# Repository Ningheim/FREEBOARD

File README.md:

# FREEBOARD
A 60% RGB Backlit Keyboard with a OLED display, rotary encoder, and adjustable inclination stands.

This keyboard is powered by an Orpheus/Raspberry Pi Pico and an additional MCP23017 for extra GPIO pins. The firmware is entirely coded in [QMK](https://qmk.fm/) and the case is a little wider than a Framework 13 for reference, at about 320x165mm it's made to be compact and accessible to be used alongside a laptop. I made this because I wanted to fix a lot of things with the layout of other wormier and logitech keyboards where the keys weren't as inline as I'd hoped whilst still including function keys and appealing RGB factors.

## Here are the pictures to the project
### Intended Layout ([Plate Generator](https://kbplate.ai03.com/)):

### Schematic (KiCAD):

### PCB (KiCAD):

### CASE (Onshape [[Document Link]](https://cad.onshape.com/documents/8cd69c605bee1d154198ffc3/w/f18789aa034f433dfb01300c/e/379cd418fcd399b0823d03fd?renderMode=0&uiState=6a71e7e218279ebdb2fef9ea))

## Case Assembly
You can use adhesive for some of the parts but it isn't required as they should sit flush without any glue, you can also sand things down to fit flush if your 3d printed had a printing issue. All of the parts I'm naming in this section have corresponding names in the onshape document.

1. Put the `Plastic Spacer` in first, then the `Plastic Window` into the slot on the inside of the `Base Case`, The window is meant to be made out of clear material like transparent plastic or something so you can see the Silkscreen design on the bottom side of the board.
2. Cut a two 1mm diameter rods to 64mm and Thread each one through the holes of each set of tilt stands you as shown in the assembly tab on the onshape document. The stands should be able to turn/revolve around the axis of the rods, and you can make the rods of any material it just has to be firm. To lock the rods in, melt plastic or insert rubber friction pads into each of the 6 empty rectangular indents on the back of the `Base Case`
3. Then you can put in the PCB with the `Plate` ontop of it. Now we have the `Top Cover` and `Translucent Emblem` left, so put the `Translucent Emblem` into the matching cutout on the `Top Cover`, and insert those joined pieces into the top of the case, to keep everything pressed down. Lastly, add the encoder knob and you're done!

## How To Flash
Freeboard uses QMK Firmware running on a Raspberry Pi Pico. The firmware source is available in firmware/freeboard.

The firmware supports:
An 81-key matrix
91 SK6812MINI-E RGB LEDs
An I2C OLED display
A rotary encoder connected through an MCP23017 GPIO expander
Media and RGB controls through a function layer

To start building the firmware, install and configure the QMK development environment, then copy the Freeboard firmware into your QMK installation:

cp -a firmware/freeboard ~/qmk_firmware/keyboards/
cd ~/qmk_firmware
qmk clean
qmk compile -kb freeboard -km default

After a successful build, the flashable firmware will be located at:

~/qmk_firmware/freeboard_default.uf2

#### Flashing Sequence
Unplug Freeboard from the computer.
Hold the BOOTSEL button on the Raspberry Pi Pico.
While continuing to hold BOOTSEL, connect the keyboard to the computer using USB.
Release BOOTSEL when a removable drive named RPI-RP2 appears.
Copy freeboard_default.uf2 onto the RPI-RP2 drive.
The drive will disconnect automatically and the keyboard will restart with the new firmware.
Flashing future updates

Hold Fn and press Esc to enter the RP2040 bootloader. When the RPI-RP2 drive appears, copy the newly compiled freeboard_default.uf2 onto it.

## CONTROLS
The Fn key is located between Right Alt and Left Arrow.

Input	Action
Rotate encoder	Adjust volume
Press encoder	Mute or unmute
Fn + Esc	Enter the bootloader
Fn + Home	Toggle RGB lighting
Fn + Page Up	Select the next RGB effect
Fn + Page Down	Select the previous RGB effect
Fn + Up	Increase RGB brightness
Fn + Down	Decrease RGB brightness
Fn + Left	Decrease RGB hue
Fn + Right	Increase RGB hue
Fn + End	Increase RGB animation speed
RGB brightness is limited in firmware because all 91 LEDs are powered from USB VBUS. Increasing the limit could exceed the available USB current.

## BOM
| Item | Cost |
|------|------|
| PCB | $37.84 |
| Switches, Keycaps, Encoder, Display | $15.00 |
| Plastic Case | Free (Printing Legion) |
| Electronic Components | $22.18 |
| Display Connector | $7.00 |
| Buffer for shipping and fees | $5.00 |
| **Total** | **~$88.02** |

Note: The BOM file itself is in ~\FREEPCB\PRODUCTION, and the keycaps, switches, stabilizers, and encoder all probably have to be bought from an external retailer. So prices may vary.

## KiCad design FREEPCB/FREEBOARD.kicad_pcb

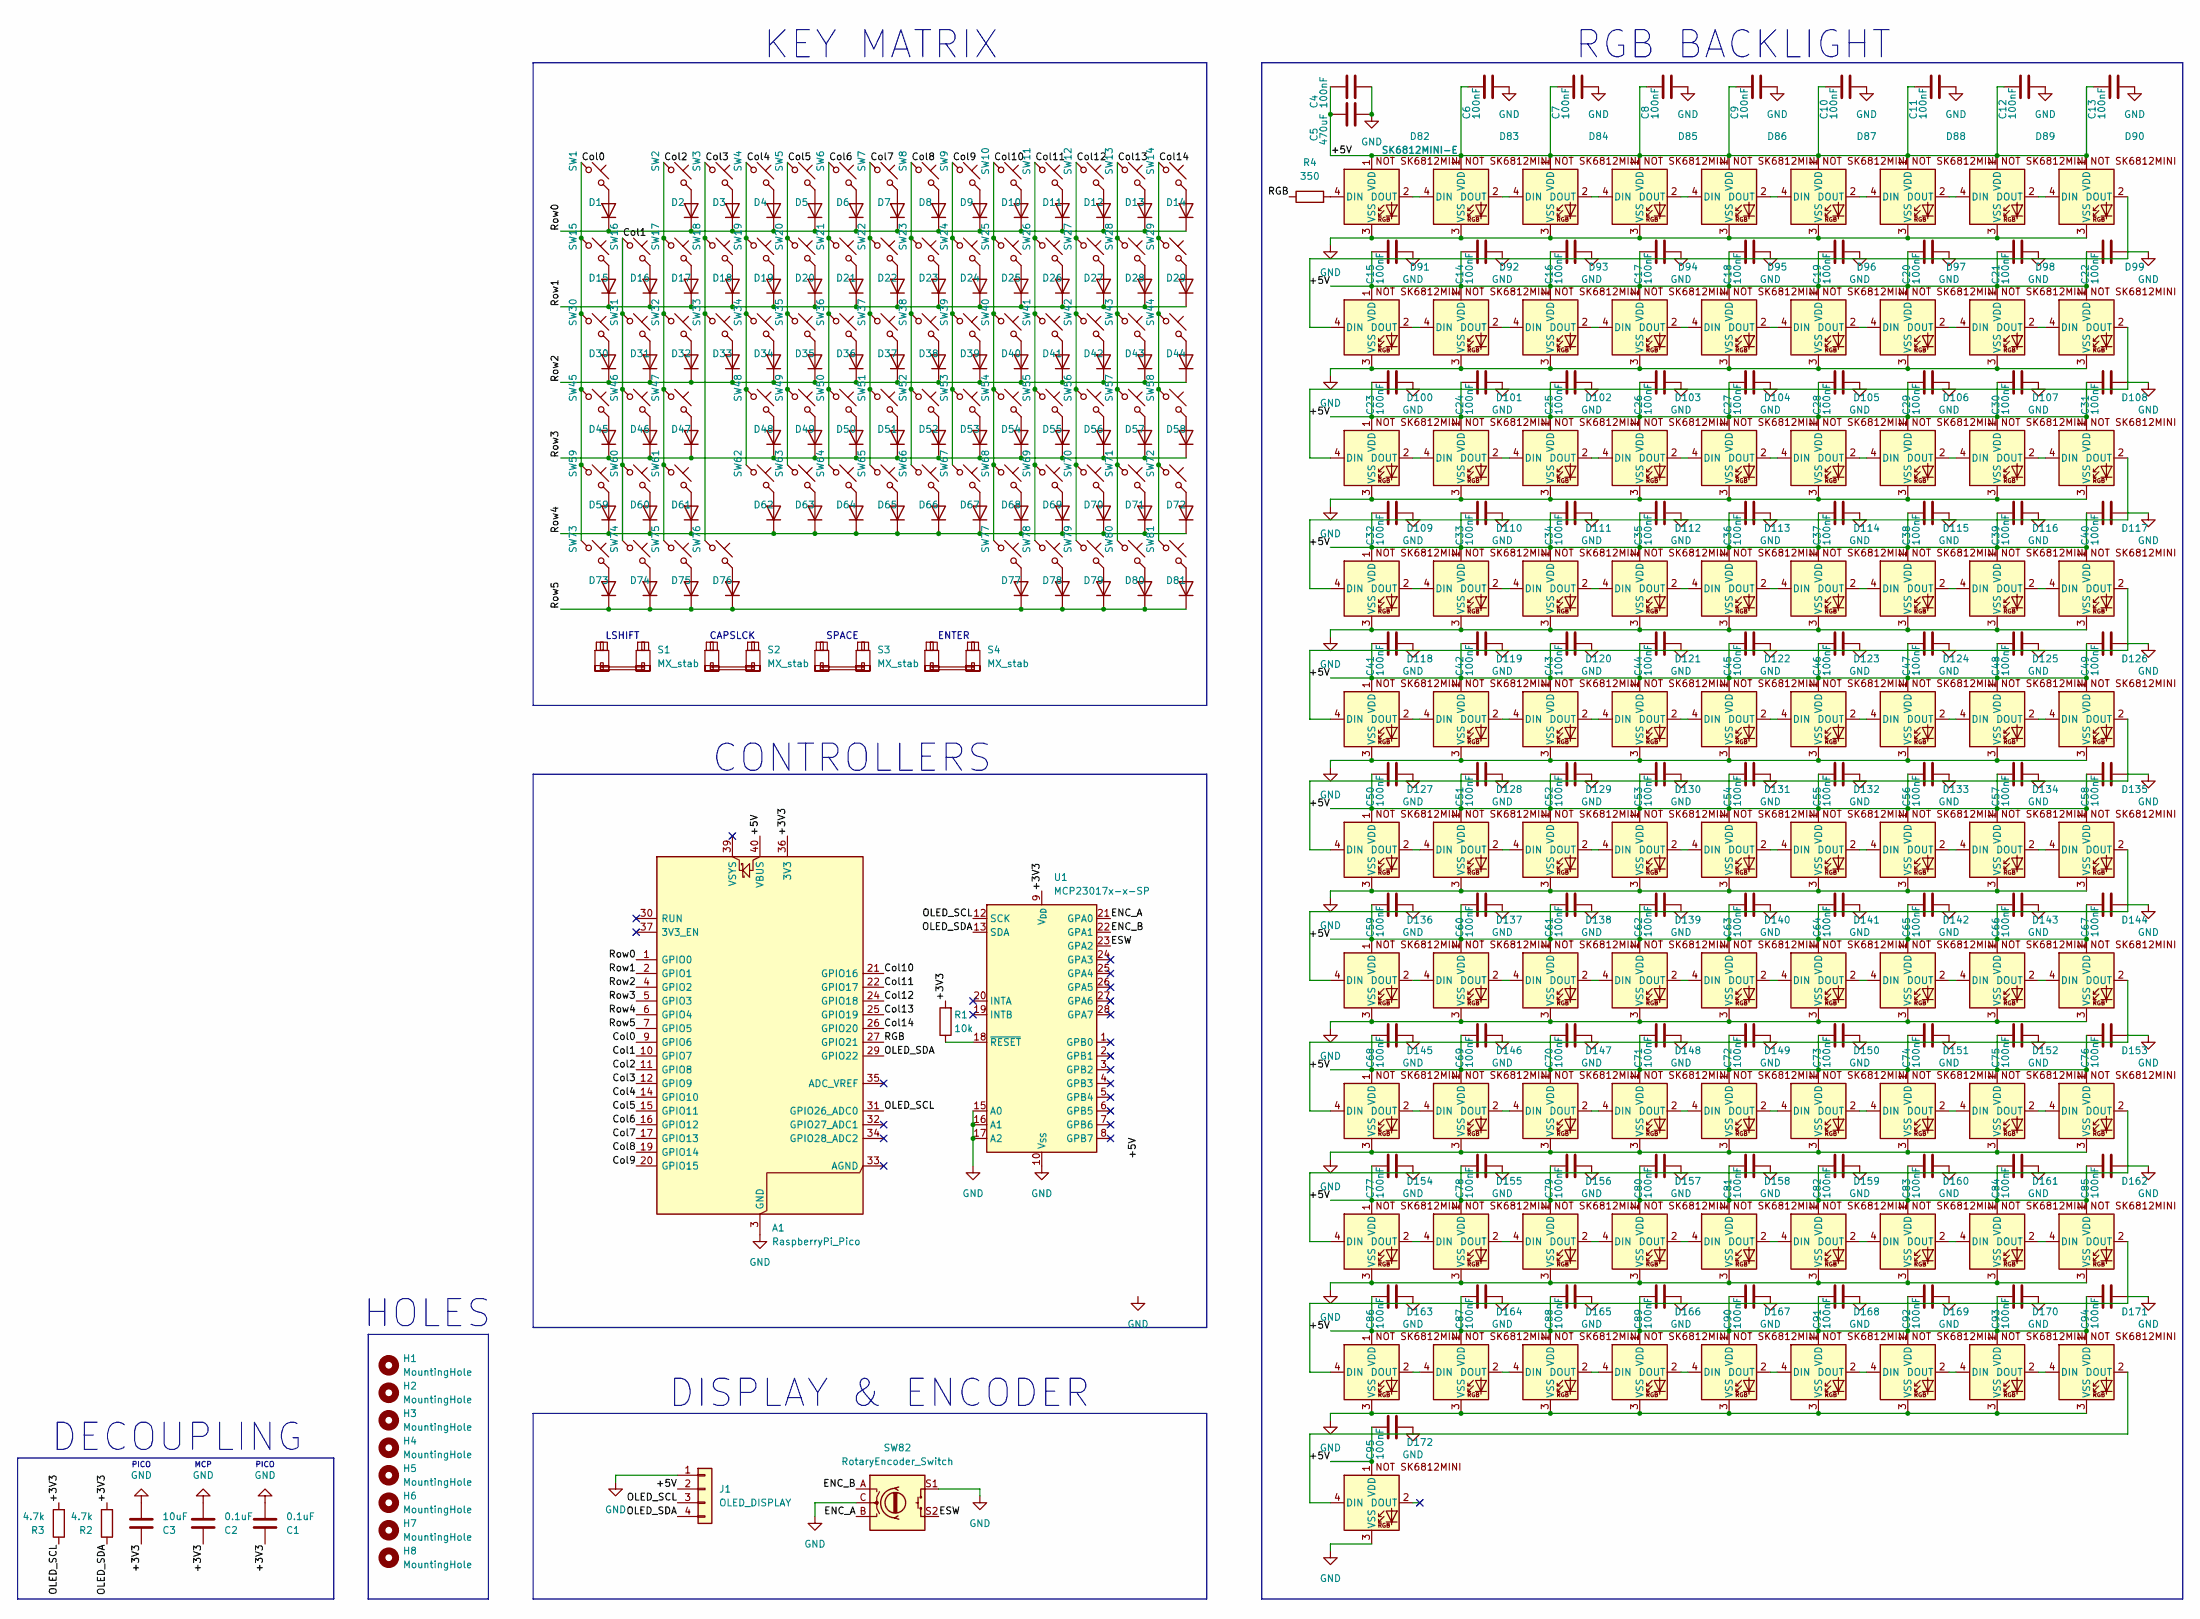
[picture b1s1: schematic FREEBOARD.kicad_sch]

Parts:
A1: RaspberryPi_Pico; RaspberryPi_Pico_Common_THT
C1, C2: 0.1uF; C_0603_1608Metric_Pad1.08x0.95mm_HandSolder
C3: 10uF; C_0805_2012Metric_Pad1.18x1.45mm_HandSolder
C4, C6, C7, C8, C9, C10, C11, C12, C13, C14, C15, C16, C17, C18, C19, C20, C21, C22, C23, C24, C25, C26, C27, C28, C29, C30, C31, C32, C33, C34, C35, C36, C37, C38, C39, C40, C41, C42, C43, C44, C45, C46, C47, C48, C49, C50, C51, C52, C53, C54, C55, C56, C57, C58, C59, C60, C61, C62, C63, C64, C65, C66, C67, C68, C69, C70, C71, C72, C73, C74, C75, C76, C77, C78, C79, C80, C81, C82, C83, C84, C85, C86, C87, C88, C89, C90, C91, C92, C93, C94, C95: 100nF; C_0603_1608Metric_Pad1.08x0.95mm_HandSolder
C5: 470uF; CP_EIA-7343-31_Kemet-D_HandSolder
D1, D2, D3, D4, D5, D6, D7, D8, D9, D10, D11, D12, D13, D14, D15, D16, D17, D18, D19, D20, D21, D22, D23, D24, D25, D26, D27, D28, D29, D30, D31, D32, D33, D34, D35, D36, D37, D38, D39, D40, D41, D42, D43, D44, D45, D46, D47, D48, D49, D50, D51, D52, D53, D54, D55, D56, D57, D58, D59, D60, D61, D62, D63, D64, D65, D66, D67, D68, D69, D70, D71, D72, D73, D74, D75, D76, D77, D78, D79, D80, D81: 1N4148; D_DO-35_SOD27_P7.62mm_Horizontal
D82, D83, D84, D85, D86, D87, D88, D89, D90, D91, D92, D93, D94, D95, D96, D97, D98, D99, D100, D101, D102, D103, D104, D105, D106, D107, D108, D109, D110, D111, D112, D113, D114, D115, D116, D117, D118, D119, D120, D121, D122, D123, D124, D125, D126, D127, D128, D129, D130, D131, D132, D133, D134, D135, D136, D137, D138, D139, D140, D141, D142, D143, D144, D145, D146, D147, D148, D149, D150, D151, D152, D153, D154, D155, D156, D157, D158, D159, D160, D161, D162, D163, D164, D165, D166, D167, D168, D169, D170, D171, D172: SK6812MINI-E; SK6812MINI-E_fixed
H1, H2, H3, H4, H5, H6, H7, H8: MountingHole; MountingHole_3.2mm_M3
J1: OLED_DISPLAY; JST_SH_BM04B-SRSS-TB_1x04-1MP_P1.00mm_Vertical
R1: 10k; R_0603_1608Metric_Pad0.98x0.95mm_HandSolder
R2, R3: 4.7k; R_0603_1608Metric_Pad0.98x0.95mm_HandSolder
R4: 350; R_0603_1608Metric_Pad0.98x0.95mm_HandSolder
S1: MX_stab; STAB_MX_2u
S2, S3: MX_stab; STAB_MX_2.25u
S4: MX_stab; STAB_MX_6.25u
SW1, SW2, SW3, SW4, SW5, SW6, SW7, SW8, SW9, SW10, SW11, SW12, SW13, SW14, SW15, SW16, SW17, SW18, SW19, SW20, SW21, SW22, SW23, SW24, SW25, SW26, SW27, SW28, SW29, SW30, SW31, SW32, SW33, SW34, SW35, SW36, SW37, SW38, SW39, SW40, SW41, SW42, SW43, SW44, SW45, SW46, SW47, SW48, SW49, SW50, SW51, SW52, SW53, SW54, SW55, SW56, SW57, SW58, SW59, SW60, SW61, SW62, SW63, SW64, SW65, SW66, SW67, SW68, SW69, SW70, SW71, SW72, SW73, SW74, SW75, SW76, SW77, SW78, SW79, SW80, SW81: SW_Push_45deg; SW_MX_1u
SW82: RotaryEncoder_Switch; ROT_Alps_EC11E-Switch
U1: MCP23017x-x-SP; DIP-28_W7.62mm

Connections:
/+3V3: A1.36 (3V3), C1.1, C2.1, C3.1, R1.2, R2.2, R3.2, U1.9 (V_{DD})
/+5V: A1.40 (VBUS), C4.1, C5.1, C6.1, C7.1, C8.1, C9.1, C10.1, C11.1, C12.1, C13.1, C14.1, C15.1, C16.1, C17.1, C18.1, C19.1, C20.1, C21.1, C22.1, C23.1, C24.1, C25.1, C26.1, C27.1, C28.1, C29.1, C30.1, C31.1, C32.1, C33.1, C34.1, C35.1, C36.1, C37.1, C38.1, C39.1, C40.1, C41.1, C42.1, C43.1, C44.1, C45.1, C46.1, C47.1, C48.1, C49.1, C50.1, C51.1, C52.1, C53.1, C54.1, C55.1, C56.1, C57.1, C58.1, C59.1, C60.1, C61.1, C62.1, C63.1, C64.1, C65.1, C66.1, C67.1, C68.1, C69.1, C70.1, C71.1, C72.1, C73.1, C74.1, C75.1, C76.1, C77.1, C78.1, C79.1, C80.1, C81.1, C82.1, C83.1, C84.1, C85.1, C86.1, C87.1, C88.1, C89.1, C90.1, C91.1, C92.1, C93.1, C94.1, C95.1, D82.1 (VDD), D83.1 (VDD), D84.1 (VDD), D85.1 (VDD), D86.1 (VDD), D87.1 (VDD), D88.1 (VDD), D89.1 (VDD), D90.1 (VDD), D91.1 (VDD), D92.1 (VDD), D93.1 (VDD), D94.1 (VDD), D95.1 (VDD), D96.1 (VDD), D97.1 (VDD), D98.1 (VDD), D99.1 (VDD), D100.1 (VDD), D101.1 (VDD), D102.1 (VDD), D103.1 (VDD), D104.1 (VDD), D105.1 (VDD), D106.1 (VDD), D107.1 (VDD), D108.1 (VDD), D109.1 (VDD), D110.1 (VDD), D111.1 (VDD), D112.1 (VDD), D113.1 (VDD), D114.1 (VDD), D115.1 (VDD), D116.1 (VDD), D117.1 (VDD), D118.1 (VDD), D119.1 (VDD), D120.1 (VDD), D121.1 (VDD), D122.1 (VDD), D123.1 (VDD), D124.1 (VDD), D125.1 (VDD), D126.1 (VDD), D127.1 (VDD), D128.1 (VDD), D129.1 (VDD), D130.1 (VDD), D131.1 (VDD), D132.1 (VDD), D133.1 (VDD), D134.1 (VDD), D135.1 (VDD), D136.1 (VDD), D137.1 (VDD), D138.1 (VDD), D139.1 (VDD), D140.1 (VDD), D141.1 (VDD), D142.1 (VDD), D143.1 (VDD), D144.1 (VDD), D145.1 (VDD), D146.1 (VDD), D147.1 (VDD), D148.1 (VDD), D149.1 (VDD), D150.1 (VDD), D151.1 (VDD), D152.1 (VDD), D153.1 (VDD), D154.1 (VDD), D155.1 (VDD), D156.1 (VDD), D157.1 (VDD), D158.1 (VDD), D159.1 (VDD), D160.1 (VDD), D161.1 (VDD), D162.1 (VDD), D163.1 (VDD), D164.1 (VDD), D165.1 (VDD), D166.1 (VDD), D167.1 (VDD), D168.1 (VDD), D169.1 (VDD), D170.1 (VDD), D171.1 (VDD), D172.1 (VDD), J1.2
/Col0: A1.9 (GPIO6), SW1.1, SW15.1, SW30.1, SW45.1, SW59.1, SW73.1
/Col1: A1.10 (GPIO7), SW16.1, SW31.1, SW46.1, SW60.1, SW74.1
/Col2: A1.11 (GPIO8), SW2.1, SW17.1, SW32.1, SW47.1, SW61.1, SW75.1
/Col3: A1.12 (GPIO9), SW3.1, SW18.1, SW33.1, SW76.1
/Col4: A1.14 (GPIO10), SW4.1, SW19.1, SW34.1, SW48.1, SW62.1
/Col5: A1.15 (GPIO11), SW5.1, SW20.1, SW35.1, SW49.1, SW63.1
/Col6: A1.16 (GPIO12), SW6.1, SW21.1, SW36.1, SW50.1, SW64.1
/Col7: A1.17 (GPIO13), SW7.1, SW22.1, SW37.1, SW51.1, SW65.1
/Col8: A1.19 (GPIO14), SW8.1, SW23.1, SW38.1, SW52.1, SW66.1
/Col9: A1.20 (GPIO15), SW9.1, SW24.1, SW39.1, SW53.1, SW67.1
/Col10: A1.21 (GPIO16), SW10.1, SW25.1, SW40.1, SW54.1, SW68.1, SW77.1
/Col11: A1.22 (GPIO17), SW11.1, SW26.1, SW41.1, SW55.1, SW69.1, SW78.1
/Col12: A1.24 (GPIO18), SW12.1, SW27.1, SW42.1, SW56.1, SW70.1, SW79.1
/Col13: A1.25 (GPIO19), SW13.1, SW28.1, SW43.1, SW57.1, SW71.1, SW80.1
/Col14: A1.26 (GPIO20), SW14.1, SW29.1, SW44.1, SW58.1, SW72.1, SW81.1
/ENC_A: SW82.B, U1.21 (GPA0)
/ENC_B: SW82.A, U1.22 (GPA1)
/ESW: SW82.S2, U1.23 (GPA2)
/OLED_SCL: A1.31 (GPIO26_ADC0), J1.3, R3.1, U1.12 (SCK)
/OLED_SDA: A1.29 (GPIO22), J1.4, R2.1, U1.13 (SDA)
/RGB: A1.27 (GPIO21), R4.1
/Row0: A1.1 (GPIO0), D1.1 (K), D2.1 (K), D3.1 (K), D4.1 (K), D5.1 (K), D6.1 (K), D7.1 (K), D8.1 (K), D9.1 (K), D10.1 (K), D11.1 (K), D12.1 (K), D13.1 (K), D14.1 (K)
/Row1: A1.2 (GPIO1), D15.1 (K), D16.1 (K), D17.1 (K), D18.1 (K), D19.1 (K), D20.1 (K), D21.1 (K), D22.1 (K), D23.1 (K), D24.1 (K), D25.1 (K), D26.1 (K), D27.1 (K), D28.1 (K), D29.1 (K)
/Row2: A1.4 (GPIO2), D30.1 (K), D31.1 (K), D32.1 (K), D33.1 (K), D34.1 (K), D35.1 (K), D36.1 (K), D37.1 (K), D38.1 (K), D39.1 (K), D40.1 (K), D41.1 (K), D42.1 (K), D43.1 (K), D44.1 (K)
/Row3: A1.5 (GPIO3), D45.1 (K), D46.1 (K), D47.1 (K), D48.1 (K), D49.1 (K), D50.1 (K), D51.1 (K), D52.1 (K), D53.1 (K), D54.1 (K), D55.1 (K), D56.1 (K), D57.1 (K), D58.1 (K)
/Row4: A1.6 (GPIO4), D59.1 (K), D60.1 (K), D61.1 (K), D62.1 (K), D63.1 (K), D64.1 (K), D65.1 (K), D66.1 (K), D67.1 (K), D68.1 (K), D69.1 (K), D70.1 (K), D71.1 (K), D72.1 (K)
/Row5: A1.7 (GPIO5), D73.1 (K), D74.1 (K), D75.1 (K), D76.1 (K), D77.1 (K), D78.1 (K), D79.1 (K), D80.1 (K), D81.1 (K)
GND: A1.3 (GND), A1.8 (GND), A1.13 (GND), A1.18 (GND), A1.23 (GND), A1.28 (GND), A1.38 (GND), C1.2, C2.2, C3.2, C4.2, C5.2, C6.2, C7.2, C8.2, C9.2, C10.2, C11.2, C12.2, C13.2, C14.2, C15.2, C16.2, C17.2, C18.2, C19.2, C20.2, C21.2, C22.2, C23.2, C24.2, C25.2, C26.2, C27.2, C28.2, C29.2, C30.2, C31.2, C32.2, C33.2, C34.2, C35.2, C36.2, C37.2, C38.2, C39.2, C40.2, C41.2, C42.2, C43.2, C44.2, C45.2, C46.2, C47.2, C48.2, C49.2, C50.2, C51.2, C52.2, C53.2, C54.2, C55.2, C56.2, C57.2, C58.2, C59.2, C60.2, C61.2, C62.2, C63.2, C64.2, C65.2, C66.2, C67.2, C68.2, C69.2, C70.2, C71.2, C72.2, C73.2, C74.2, C75.2, C76.2, C77.2, C78.2, C79.2, C80.2, C81.2, C82.2, C83.2, C84.2, C85.2, C86.2, C87.2, C88.2, C89.2, C90.2, C91.2, C92.2, C93.2, C94.2, C95.2, D82.3 (VSS), D83.3 (VSS), D84.3 (VSS), D85.3 (VSS), D86.3 (VSS), D87.3 (VSS), D88.3 (VSS), D89.3 (VSS), D90.3 (VSS), D91.3 (VSS), D92.3 (VSS), D93.3 (VSS), D94.3 (VSS), D95.3 (VSS), D96.3 (VSS), D97.3 (VSS), D98.3 (VSS), D99.3 (VSS), D100.3 (VSS), D101.3 (VSS), D102.3 (VSS), D103.3 (VSS), D104.3 (VSS), D105.3 (VSS), D106.3 (VSS), D107.3 (VSS), D108.3 (VSS), D109.3 (VSS), D110.3 (VSS), D111.3 (VSS), D112.3 (VSS), D113.3 (VSS), D114.3 (VSS), D115.3 (VSS), D116.3 (VSS), D117.3 (VSS), D118.3 (VSS), D119.3 (VSS), D120.3 (VSS), D121.3 (VSS), D122.3 (VSS), D123.3 (VSS), D124.3 (VSS), D125.3 (VSS), D126.3 (VSS), D127.3 (VSS), D128.3 (VSS), D129.3 (VSS), D130.3 (VSS), D131.3 (VSS), D132.3 (VSS), D133.3 (VSS), D134.3 (VSS), D135.3 (VSS), D136.3 (VSS), D137.3 (VSS), D138.3 (VSS), D139.3 (VSS), D140.3 (VSS), D141.3 (VSS), D142.3 (VSS), D143.3 (VSS), D144.3 (VSS), D145.3 (VSS), D146.3 (VSS), D147.3 (VSS), D148.3 (VSS), D149.3 (VSS), D150.3 (VSS), D151.3 (VSS), D152.3 (VSS), D153.3 (VSS), D154.3 (VSS), D155.3 (VSS), D156.3 (VSS), D157.3 (VSS), D158.3 (VSS), D159.3 (VSS), D160.3 (VSS), D161.3 (VSS), D162.3 (VSS), D163.3 (VSS), D164.3 (VSS), D165.3 (VSS), D166.3 (VSS), D167.3 (VSS), D168.3 (VSS), D169.3 (VSS), D170.3 (VSS), D171.3 (VSS), D172.3 (VSS), J1.1, SW82.C, SW82.S1, U1.10 (V_{SS}), U1.15 (A0), U1.16 (A1), U1.17 (A2)
unnamed: D1.2 (A), SW1.2
unnamed: D2.2 (A), SW2.2
unnamed: D3.2 (A), SW3.2
unnamed: D4.2 (A), SW4.2
unnamed: D5.2 (A), SW5.2
unnamed: D6.2 (A), SW6.2
unnamed: D7.2 (A), SW7.2
unnamed: D8.2 (A), SW8.2
unnamed: D9.2 (A), SW9.2
unnamed: D10.2 (A), SW10.2
unnamed: D11.2 (A), SW11.2
unnamed: D12.2 (A), SW12.2
unnamed: D13.2 (A), SW13.2
unnamed: D14.2 (A), SW14.2
unnamed: D15.2 (A), SW15.2
unnamed: D16.2 (A), SW16.2
unnamed: D17.2 (A), SW17.2
unnamed: D18.2 (A), SW18.2
unnamed: D19.2 (A), SW19.2
unnamed: D20.2 (A), SW20.2
unnamed: D21.2 (A), SW21.2
unnamed: D22.2 (A), SW22.2
unnamed: D23.2 (A), SW23.2
unnamed: D24.2 (A), SW24.2
unnamed: D25.2 (A), SW25.2
unnamed: D26.2 (A), SW26.2
unnamed: D27.2 (A), SW27.2
unnamed: D28.2 (A), SW28.2
unnamed: D29.2 (A), SW29.2
unnamed: D30.2 (A), SW30.2
unnamed: D31.2 (A), SW31.2
unnamed: D32.2 (A), SW32.2
unnamed: D33.2 (A), SW33.2
unnamed: D34.2 (A), SW34.2
unnamed: D35.2 (A), SW35.2
unnamed: D36.2 (A), SW36.2
unnamed: D37.2 (A), SW37.2
unnamed: D38.2 (A), SW38.2
unnamed: D39.2 (A), SW39.2
unnamed: D40.2 (A), SW40.2
unnamed: D41.2 (A), SW41.2
unnamed: D42.2 (A), SW42.2
unnamed: D43.2 (A), SW43.2
unnamed: D44.2 (A), SW44.2
unnamed: D45.2 (A), SW45.2
unnamed: D46.2 (A), SW46.2
unnamed: D47.2 (A), SW47.2
unnamed: D48.2 (A), SW48.2
unnamed: D49.2 (A), SW49.2
unnamed: D50.2 (A), SW50.2
unnamed: D51.2 (A), SW51.2
unnamed: D52.2 (A), SW52.2
unnamed: D53.2 (A), SW53.2
unnamed: D54.2 (A), SW54.2
unnamed: D55.2 (A), SW55.2
unnamed: D56.2 (A), SW56.2
unnamed: D57.2 (A), SW57.2
unnamed: D58.2 (A), SW58.2
unnamed: D59.2 (A), SW59.2
unnamed: D60.2 (A), SW60.2
unnamed: D61.2 (A), SW61.2
unnamed: D62.2 (A), SW62.2
unnamed: D63.2 (A), SW63.2
unnamed: D64.2 (A), SW64.2
unnamed: D65.2 (A), SW65.2
unnamed: D66.2 (A), SW66.2
unnamed: D67.2 (A), SW67.2
unnamed: D68.2 (A), SW68.2
unnamed: D69.2 (A), SW69.2
unnamed: D70.2 (A), SW70.2
unnamed: D71.2 (A), SW71.2
unnamed: D72.2 (A), SW72.2
unnamed: D73.2 (A), SW73.2
unnamed: D74.2 (A), SW74.2
unnamed: D75.2 (A), SW75.2
unnamed: D76.2 (A), SW76.2
unnamed: D77.2 (A), SW77.2
unnamed: D78.2 (A), SW78.2
unnamed: D79.2 (A), SW79.2
unnamed: D80.2 (A), SW80.2
unnamed: D81.2 (A), SW81.2
unnamed: D82.4 (DIN), R4.2
unnamed: D82.2 (DOUT), D83.4 (DIN)
unnamed: D83.2 (DOUT), D84.4 (DIN)
unnamed: D84.2 (DOUT), D85.4 (DIN)
unnamed: D85.2 (DOUT), D86.4 (DIN)
unnamed: D86.2 (DOUT), D87.4 (DIN)
unnamed: D87.2 (DOUT), D88.4 (DIN)
unnamed: D88.2 (DOUT), D89.4 (DIN)
unnamed: D89.2 (DOUT), D90.4 (DIN)
unnamed: D90.2 (DOUT), D91.4 (DIN)
unnamed: D91.2 (DOUT), D92.4 (DIN)
unnamed: D92.2 (DOUT), D93.4 (DIN)
unnamed: D93.2 (DOUT), D94.4 (DIN)
unnamed: D94.2 (DOUT), D95.4 (DIN)
unnamed: D95.2 (DOUT), D96.4 (DIN)
unnamed: D96.2 (DOUT), D97.4 (DIN)
unnamed: D97.2 (DOUT), D98.4 (DIN)
unnamed: D98.2 (DOUT), D99.4 (DIN)
unnamed: D99.2 (DOUT), D100.4 (DIN)
unnamed: D100.2 (DOUT), D101.4 (DIN)
unnamed: D101.2 (DOUT), D102.4 (DIN)
unnamed: D102.2 (DOUT), D103.4 (DIN)
unnamed: D103.2 (DOUT), D104.4 (DIN)
unnamed: D104.2 (DOUT), D105.4 (DIN)
unnamed: D105.2 (DOUT), D106.4 (DIN)
unnamed: D106.2 (DOUT), D107.4 (DIN)
unnamed: D107.2 (DOUT), D108.4 (DIN)
unnamed: D108.2 (DOUT), D109.4 (DIN)
unnamed: D109.2 (DOUT), D110.4 (DIN)
unnamed: D110.2 (DOUT), D111.4 (DIN)
unnamed: D111.2 (DOUT), D112.4 (DIN)
unnamed: D112.2 (DOUT), D113.4 (DIN)
unnamed: D113.2 (DOUT), D114.4 (DIN)
unnamed: D114.2 (DOUT), D115.4 (DIN)
unnamed: D115.2 (DOUT), D116.4 (DIN)
unnamed: D116.2 (DOUT), D117.4 (DIN)
unnamed: D117.2 (DOUT), D118.4 (DIN)
unnamed: D118.2 (DOUT), D119.4 (DIN)
unnamed: D119.2 (DOUT), D120.4 (DIN)
unnamed: D120.2 (DOUT), D121.4 (DIN)
unnamed: D121.2 (DOUT), D122.4 (DIN)
unnamed: D122.2 (DOUT), D123.4 (DIN)
unnamed: D123.2 (DOUT), D124.4 (DIN)
unnamed: D124.2 (DOUT), D125.4 (DIN)
unnamed: D125.2 (DOUT), D126.4 (DIN)
unnamed: D126.2 (DOUT), D127.4 (DIN)
unnamed: D127.2 (DOUT), D128.4 (DIN)
unnamed: D128.2 (DOUT), D129.4 (DIN)
unnamed: D129.2 (DOUT), D130.4 (DIN)
unnamed: D130.2 (DOUT), D131.4 (DIN)
unnamed: D131.2 (DOUT), D132.4 (DIN)
unnamed: D132.2 (DOUT), D133.4 (DIN)
unnamed: D133.2 (DOUT), D134.4 (DIN)
unnamed: D134.2 (DOUT), D135.4 (DIN)
unnamed: D135.2 (DOUT), D136.4 (DIN)
unnamed: D136.2 (DOUT), D137.4 (DIN)
unnamed: D137.2 (DOUT), D138.4 (DIN)
unnamed: D138.2 (DOUT), D139.4 (DIN)
unnamed: D139.2 (DOUT), D140.4 (DIN)
unnamed: D140.2 (DOUT), D141.4 (DIN)
unnamed: D141.2 (DOUT), D142.4 (DIN)
unnamed: D142.2 (DOUT), D143.4 (DIN)
unnamed: D143.2 (DOUT), D144.4 (DIN)
unnamed: D144.2 (DOUT), D145.4 (DIN)
unnamed: D145.2 (DOUT), D146.4 (DIN)
unnamed: D146.2 (DOUT), D147.4 (DIN)
unnamed: D147.2 (DOUT), D148.4 (DIN)
unnamed: D148.2 (DOUT), D149.4 (DIN)
unnamed: D149.2 (DOUT), D150.4 (DIN)
unnamed: D150.2 (DOUT), D151.4 (DIN)
unnamed: D151.2 (DOUT), D152.4 (DIN)
unnamed: D152.2 (DOUT), D153.4 (DIN)
unnamed: D153.2 (DOUT), D154.4 (DIN)
unnamed: D154.2 (DOUT), D155.4 (DIN)
unnamed: D155.2 (DOUT), D156.4 (DIN)
unnamed: D156.2 (DOUT), D157.4 (DIN)
unnamed: D157.2 (DOUT), D158.4 (DIN)
unnamed: D158.2 (DOUT), D159.4 (DIN)
unnamed: D159.2 (DOUT), D160.4 (DIN)
unnamed: D160.2 (DOUT), D161.4 (DIN)
unnamed: D161.2 (DOUT), D162.4 (DIN)
unnamed: D162.2 (DOUT), D163.4 (DIN)
unnamed: D163.2 (DOUT), D164.4 (DIN)
unnamed: D164.2 (DOUT), D165.4 (DIN)
unnamed: D165.2 (DOUT), D166.4 (DIN)
unnamed: D166.2 (DOUT), D167.4 (DIN)
unnamed: D167.2 (DOUT), D168.4 (DIN)
unnamed: D168.2 (DOUT), D169.4 (DIN)
unnamed: D169.2 (DOUT), D170.4 (DIN)
unnamed: D170.2 (DOUT), D171.4 (DIN)
unnamed: D171.2 (DOUT), D172.4 (DIN)
unnamed: R1.1, U1.18 (~RESET)

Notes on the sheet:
SPACE
DISPLAY & ENCODER
PICO
ENTER
CONTROLLERS
RGB BACKLIGHT
LSHIFT
DECOUPLING
KEY MATRIX
HOLES
CAPSLCK
MCP

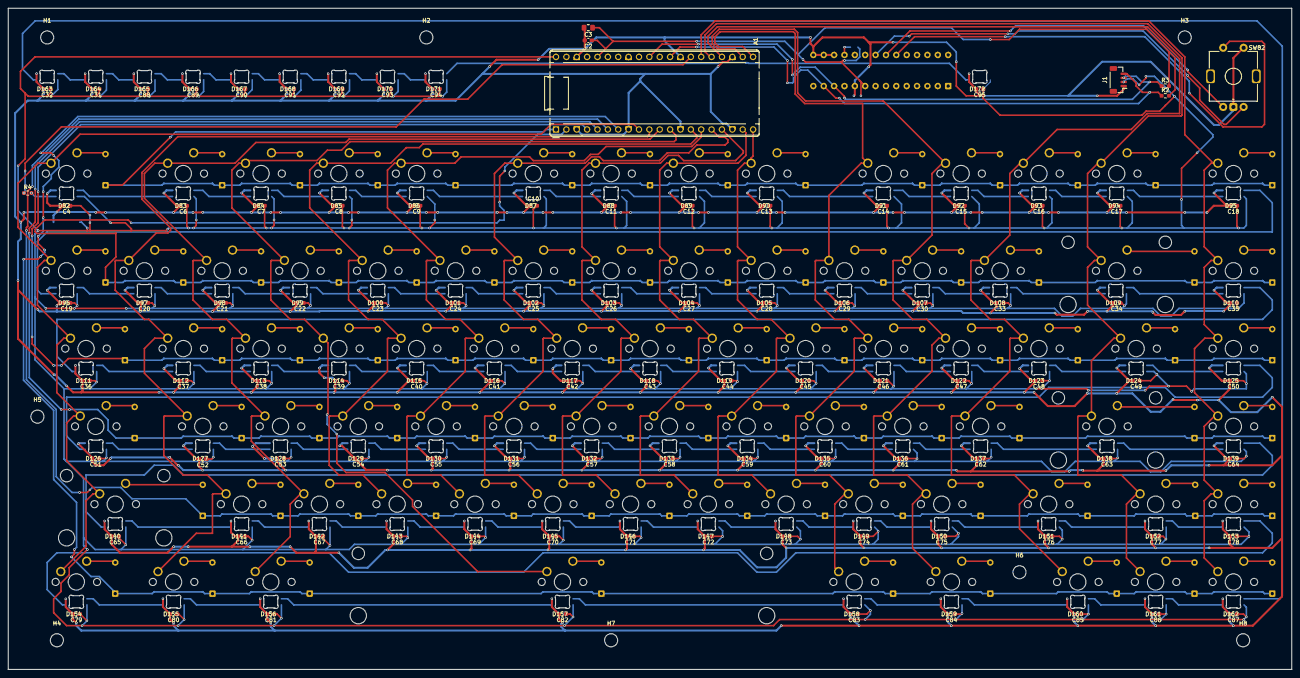
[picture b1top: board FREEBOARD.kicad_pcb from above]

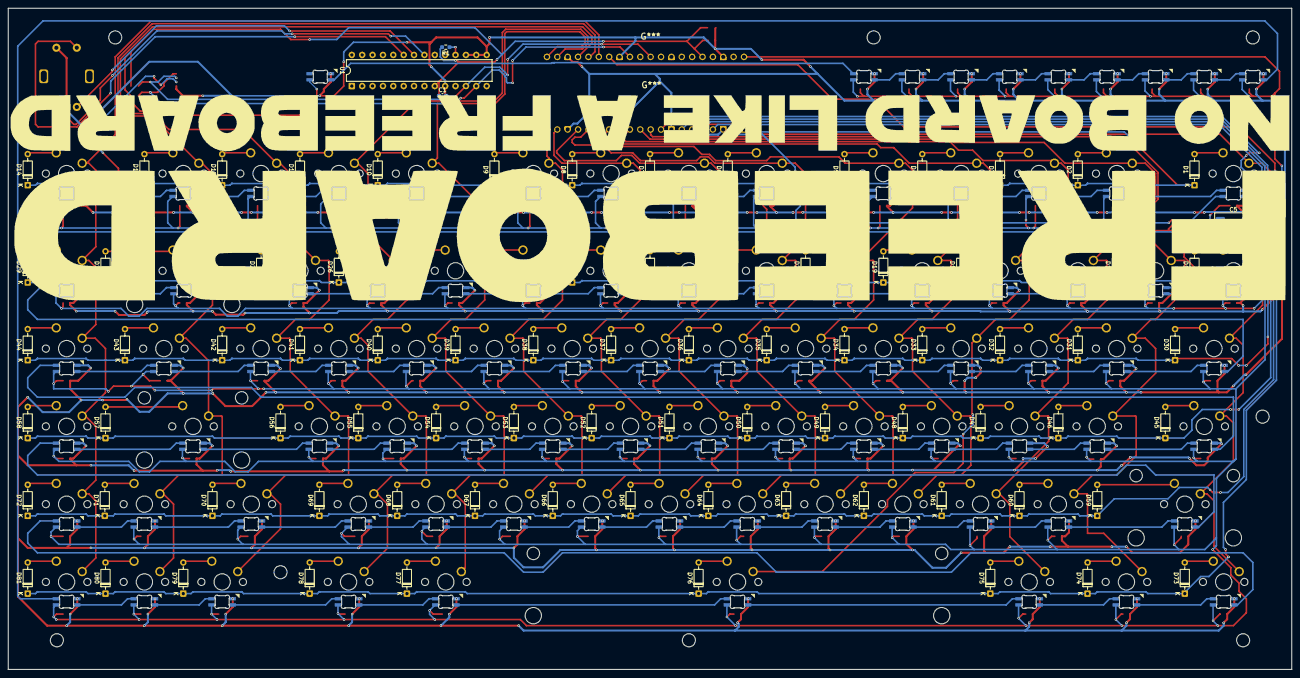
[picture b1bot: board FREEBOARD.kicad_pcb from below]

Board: 2 copper layers, 314.3 x 161.9 mm, 368 parts (85 on the bottom side), 203 nets.

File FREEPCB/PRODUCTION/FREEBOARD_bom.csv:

Designator,Footprint,Quantity,Value,LCSC Part #
A1,RaspberryPi_Pico_Common_THT,1,RaspberryPi_Pico,
"C1, C2",0603,2,0.1uF,
"C10, C11, C12, C13, C14, C15, C16, C17, C18, C19, C20, C21, C22, C23, C24, C25, C26, C27, C28, C29, C30, C31, C32, C33, C34, C35, C36, C37, C38, C39, C4, C40, C41, C42, C43, C44, C45, C46, C47, C48, C49, C50, C51, C52, C53, C54, C55, C56, C57, C58, C59, C6, C60, C61, C62, C63, C64, C65, C66, C67, C68, C69, C7, C70, C71, C72, C73, C74, C75, C76, C77, C78, C79, C8, C80, C81, C82, C83, C84, C85, C86, C87, C88, C89, C9, C90, C91, C92, C93, C94, C95",0603,91,100nF,
C3,0805,1,10uF,
C5,CP_EIA-7343-31_Kemet-D_HandSolder,1,470uF,
"D1, D10, D11, D12, D13, D14, D15, D16, D17, D18, D19, D2, D20, D21, D22, D23, D24, D25, D26, D27, D28, D29, D3, D30, D31, D32, D33, D34, D35, D36, D37, D38, D39, D4, D40, D41, D42, D43, D44, D45, D46, D47, D48, D49, D5, D50, D51, D52, D53, D54, D55, D56, D57, D58, D59, D6, D60, D61, D62, D63, D64, D65, D66, D67, D68, D69, D7, D70, D71, D72, D73, D74, D75, D76, D77, D78, D79, D8, D80, D81, D9",D_DO-35_SOD27_P7.62mm_Horizontal,81,1N4148,
"D100, D101, D102, D103, D104, D105, D106, D107, D108, D109, D110, D111, D112, D113, D114, D115, D116, D117, D118, D119, D120, D121, D122, D123, D124, D125, D126, D127, D128, D129, D130, D131, D132, D133, D134, D135, D136, D137, D138, D139, D140, D141, D142, D143, D144, D145, D146, D147, D148, D149, D150, D151, D152, D153, D154, D155, D156, D157, D158, D159, D160, D161, D162, D163, D164, D165, D166, D167, D168, D169, D170, D171, D172, D82, D83, D84, D85, D86, D87, D88, D89, D90, D91, D92, D93, D94, D95, D96, D97, D98, D99",SK6812MINI-E_fixed,91,SK6812MINI-E,
J1,JST_SH_BM04B-SRSS-TB_1x04-1MP_P1.00mm_Vertical,1,OLED_DISPLAY,
R1,0603,1,10k,
"R2, R3",0603,2,4.7k,
R4,0603,1,350,
S1,STAB_MX_2u,1,MX_stab,
"S2, S3",STAB_MX_2.25u,2,MX_stab,
S4,STAB_MX_6.25u,1,MX_stab,
"SW1, SW10, SW11, SW12, SW13, SW14, SW15, SW16, SW17, SW18, SW19, SW2, SW20, SW21, SW22, SW23, SW24, SW25, SW26, SW27, SW28, SW29, SW3, SW30, SW31, SW32, SW33, SW34, SW35, SW36, SW37, SW38, SW39, SW4, SW40, SW41, SW42, SW43, SW44, SW45, SW46, SW47, SW48, SW49, SW5, SW50, SW51, SW52, SW53, SW54, SW55, SW56, SW57, SW58, SW59, SW6, SW60, SW61, SW62, SW63, SW64, SW65, SW66, SW67, SW68, SW69, SW7, SW70, SW71, SW72, SW73, SW74, SW75, SW76, SW77, SW78, SW79, SW8, SW80, SW81, SW9",SW_MX_1u,81,SW_Push_45deg,
SW82,ROT_Alps_EC11E-Switch,1,RotaryEncoder_Switch,
U1,DIP-28_W7.62mm,1,MCP23017x-x-SP,
